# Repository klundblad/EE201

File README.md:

# This is section A

## more stuff

This is a line

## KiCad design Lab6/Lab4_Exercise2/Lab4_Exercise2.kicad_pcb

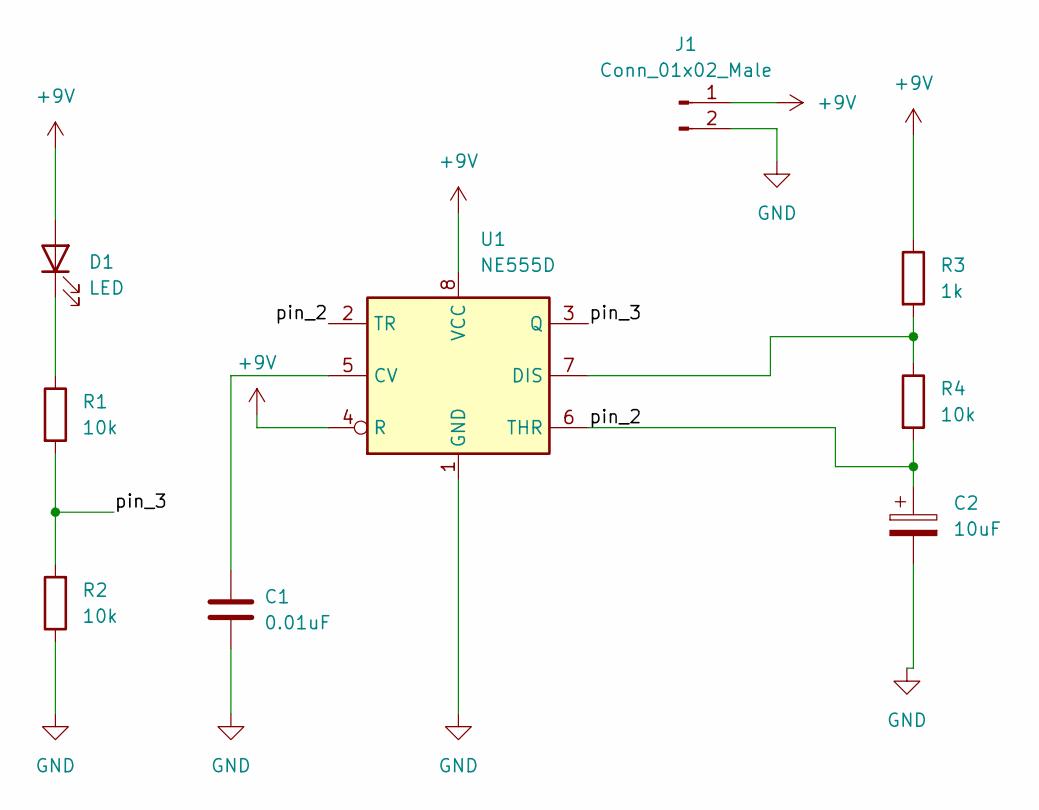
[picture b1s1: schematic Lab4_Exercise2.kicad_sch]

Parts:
C1: 0.01uF
C2: 10uF
D1: LED
J1: Conn_01x02_Male
R1, R2, R4: 10k
R3: 1k
U1: NE555D; SOIC-8_3.9x4.9mm_P1.27mm

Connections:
+9V: D1.2 (A), J1.1, R3.1, U1.4 (R), U1.8 (VCC)
/pin_2: C2.1, R4.2, U1.2 (TR), U1.6 (THR)
/pin_3: R1.2, R2.2, U1.3 (Q)
GND: C1.2, C2.2, J1.2, R2.1, U1.1 (GND)
unnamed: C1.1, U1.5 (CV)
unnamed: D1.1 (K), R1.1
unnamed: R3.2, R4.1, U1.7 (DIS)

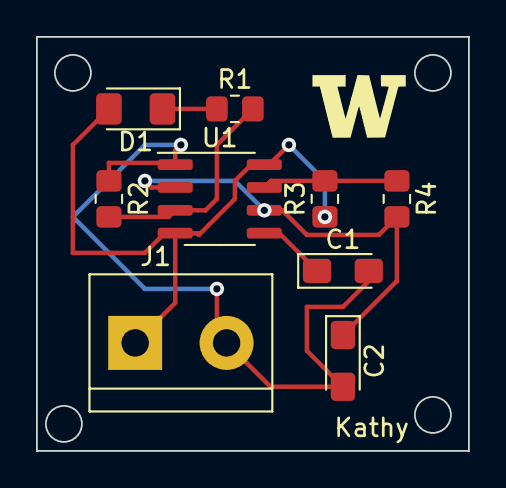
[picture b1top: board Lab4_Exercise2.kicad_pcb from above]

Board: 2 copper layers, 24.0 x 23.0 mm, 9 parts (0 on the bottom side), 7 nets.

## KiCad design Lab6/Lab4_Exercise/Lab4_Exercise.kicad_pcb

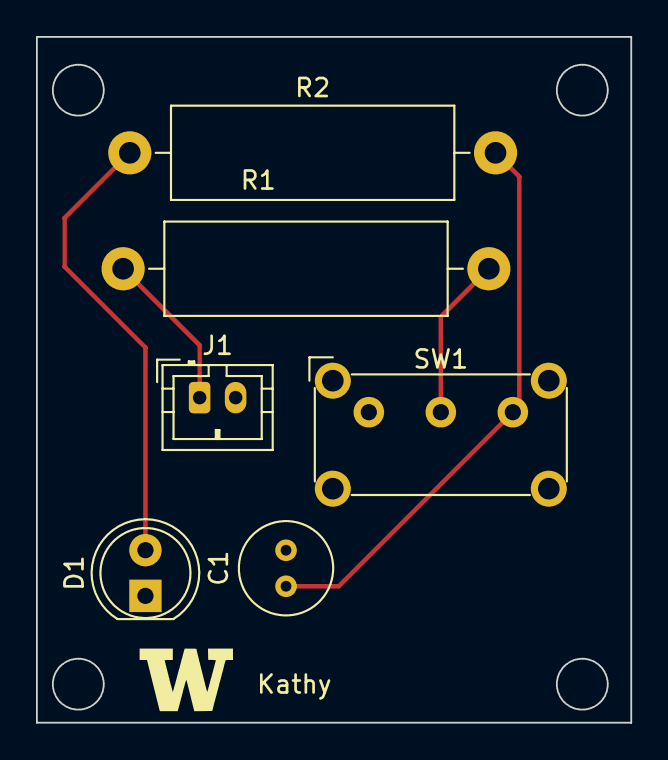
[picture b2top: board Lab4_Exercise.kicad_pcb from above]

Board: 2 copper layers, 33.0 x 38.1 mm, 6 parts (0 on the bottom side), 5 nets.

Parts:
C1: 4.7u; C_Radial_D5.0mm_H5.0mm_P2.00mm
D1: LED; LED_D5.0mm
J1: Conn_01x02_Male; JST_PH_B2B-PH-K_1x02_P2.00mm_Vertical
R1: 2.2k; R_Axial_DIN0516_L15.5mm_D5.0mm_P20.32mm_Horizontal
R2: 20k; R_Axial_DIN0516_L15.5mm_D5.0mm_P20.32mm_Horizontal
SW1: SW_SPDT; SW_E-Switch_EG1224_SPDT_Angled

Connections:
+9V: J1.1, R1.1
GND: C1.2, D1.1 (K), J1.2
unnamed: C1.1, R2.2, SW1.3 (C)
unnamed: D1.2 (A), R2.1
unnamed: R1.2, SW1.2 (B)

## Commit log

2023-01-10 My first repogit add -A
2023-01-10 Type commit message
2023-01-10 New folder created
2023-01-10 new folder added
2023-01-10 Git Exercise assignment for EE 201
2023-01-17 Added arduino exercises for blinking the LED and 7 seg display
2023-01-17 Added comments
2023-01-18 Deleted Arduino
2023-01-18 Added Arduino to correct branch
2023-01-24 Added KiCAD exercise from class
2023-01-24 Edited Lab 4 KiCAD files
2023-01-31 Added annotations
2023-02-07 Added place and routed Exercises 1 and 2 for Lab 6
2023-02-21 Added Gerber Files
2023-03-11 Added link to demo for the Arduino Multimeter
